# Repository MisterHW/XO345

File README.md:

# XO345
is a drop-in replacement for FT245 that eliminates USB in favor of a single SPI slave interface - making USB peripherals embedded peripherals without USB host and device driver. Initially developed on a MachXO2-7000HE board (hence XO245), then ported and tested with MachXO3L-1300E and MachXO3LF-6900C (renamed to XO345).

In its final implementation, a WLCSP MachXO3-1300E sits on a QFP-32 sized PCB with castellations and directly connects to the former FT245 pads. Its crystal is removed and additional signals are routed out on these pins.

PCB files will be uploaded here as well, for now please check out https://hackaday.io/project/9547-xo245

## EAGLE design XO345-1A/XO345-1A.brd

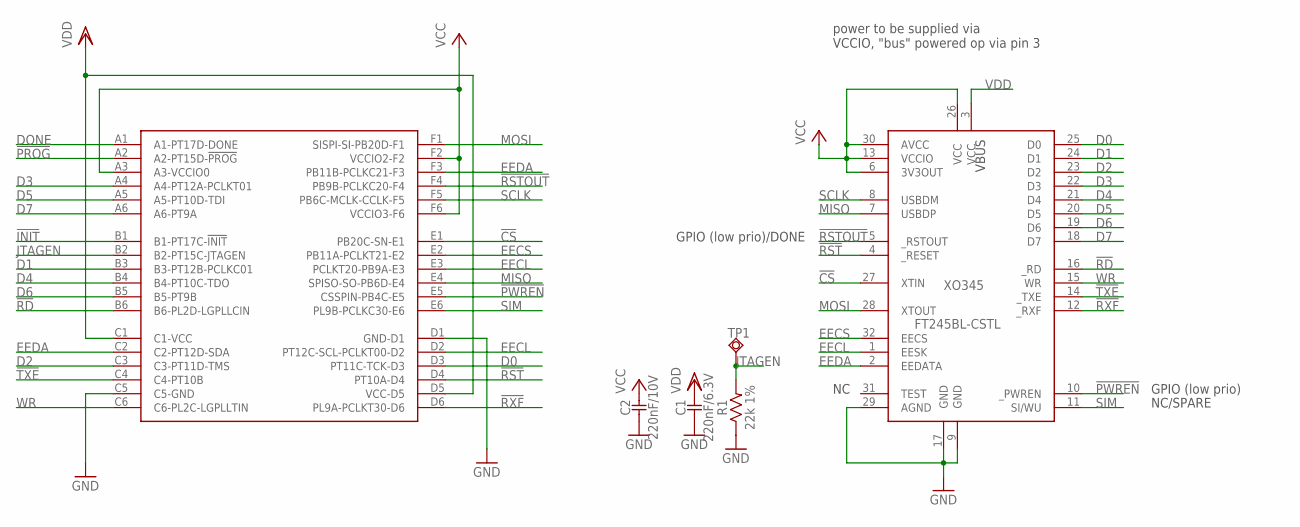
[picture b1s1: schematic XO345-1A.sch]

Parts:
C1: 220nF/6.3V; C0402; MFG_PARTNO C1005X5R1A224M050BC; MOUSER 810-C1005X5R1A224M
C2: 220nF/10V; C0603
IC: XO3-LCSP36; WLCSP36; MFG_PARTNO LCMXO3L-1300E-5UWG36CTR50; MOUSER 842-XO3L13E5U36CTR50
R1: 22k 1%; R0402; MFG_PARTNO CRCW04022K70FKED; MOUSER 71-CRCW0402-2.7K-E3
TP1: TPSQTP06R; TP06R
XO345: FT245BL-CSTL; LQFP-32-CAST

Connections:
!CS: IC.E1 (PB20C-SN-E1), XO345.27 (XTIN)
!INIT: IC.B1 (B1-PT17C-!INIT!)
!PROG: IC.A2 (A2-PT15D-!PROG!)
!PWREN: IC.E5 (CSSPIN-PB4C-E5), XO345.10 (_PWREN)
!RD: IC.B6 (B6-PL2D-LGPLLCIN), XO345.16 (_RD)
!RST: IC.D4 (PT10A-D4), XO345.4 (_RESET)
!RSTOUT: IC.F4 (PB9B-PCLKC20-F4), XO345.5 (_RSTOUT)
!RXF: IC.D6 (PL9A-PCLKT30-D6), XO345.12 (_RXF)
!TXE: IC.C4 (C4-PT10B), XO345.14 (_TXE)
D0: IC.D3 (PT11C-TCK-D3), XO345.25 (D0)
D1: IC.B3 (B3-PT12B-PCLKC01), XO345.24 (D1)
D2: IC.C3 (C3-PT11D-TMS), XO345.23 (D2)
D3: IC.A4 (A4-PT12A-PCLKT01), XO345.22 (D3)
D4: IC.B4 (B4-PT10C-TDO), XO345.21 (D4)
D5: IC.A5 (A5-PT10D-TDI), XO345.20 (D5)
D6: IC.B5 (B5-PT9B), XO345.19 (D6)
D7: IC.A6 (A6-PT9A), XO345.18 (D7)
DONE: IC.A1 (A1-PT17D-DONE)
EECL: IC.D2 (PT12C-SCL-PCLKT00-D2), IC.E3 (PCLKT20-PB9A-E3), XO345.1 (EESK)
EECS: IC.E2 (PB11A-PCLKT21-E2), XO345.32 (EECS)
EEDA: IC.C2 (C2-PT12D-SDA), IC.F3 (PB11B-PCLKC21-F3), XO345.2 (EEDATA)
GND: C1.1, C2.1, IC.C5 (C5-GND), IC.D1 (GND-D1), R1.1, XO345.9 (GND), XO345.17 (GND), XO345.29 (AGND)
JTAGEN: IC.B2 (B2-PT15C-JTAGEN), R1.2, TP1.TP
MISO: IC.E4 (SPISO-SO-PB6D-E4), XO345.7 (USBDP)
MOSI: IC.F1 (SISPI-SI-PB20D-F1), XO345.28 (XTOUT)
SCLK: IC.F5 (PB6C-MCLK-CCLK-F5), XO345.8 (USBDM)
SIM: IC.E6 (PL9B-PCLKC30-E6), XO345.11 (SI/WU)
VCC: C2.2, IC.A3 (A3-VCCIO0), IC.F2 (VCCIO2-F2), IC.F6 (VCCIO3-F6), XO345.6 (3V3OUT), XO345.13 (VCCIO), XO345.26 (VCC), XO345.30 (AVCC)
VDD: C1.2, IC.C1 (C1-VCC), IC.D5 (VCC-D5), XO345.3 (VCC)
WR: IC.C6 (C6-PL2C-LGPLLTIN), XO345.15 (WR)

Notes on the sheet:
power to be supplied via VCCIO, "bus" powered op via pin 3
VBUS
NC/SPARE
GPIO (low prio)
GPIO (low prio)/DONE

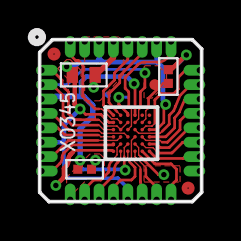
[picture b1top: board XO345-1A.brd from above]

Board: 2 copper layers, 9.0 x 9.0 mm, 6 parts (0 on the bottom side), 27 nets.

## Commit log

2018-02-07 Add files via upload
    specs sheet and board revisions 1A (has !CS errorenously connected to SN which is a sysIO that, as it turned out, cannot be made general purpose IO while simultaneously using the SPI EFB... sad becau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
    The test pad is there to enable JTAG (needs to be pulled high, otherwise JTAG is repurposed for the 245 interface.
